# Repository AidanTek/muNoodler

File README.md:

# µNoodler Project
## Technical Files and Info for the µNoodler SAMD21G18A breakout

This project is for me to learn about a number of things, the idea being to build a SAMD21G18A MCU breakout from the ground up that can be used for Circuit Python, MicroPython or Arduino programming. You are welcome to use the files here for anything you want. 

This project was and is possible because of the amazing contributions towards OSH from Adafruit and Arduino - in support, please buy genuine products from these companies!

This is a work in progress! Aidan Taylor 2019

See the installation guide if you have a muNoodler board to experiment with. The Sketch directory provides code examples - contributions are welcome!

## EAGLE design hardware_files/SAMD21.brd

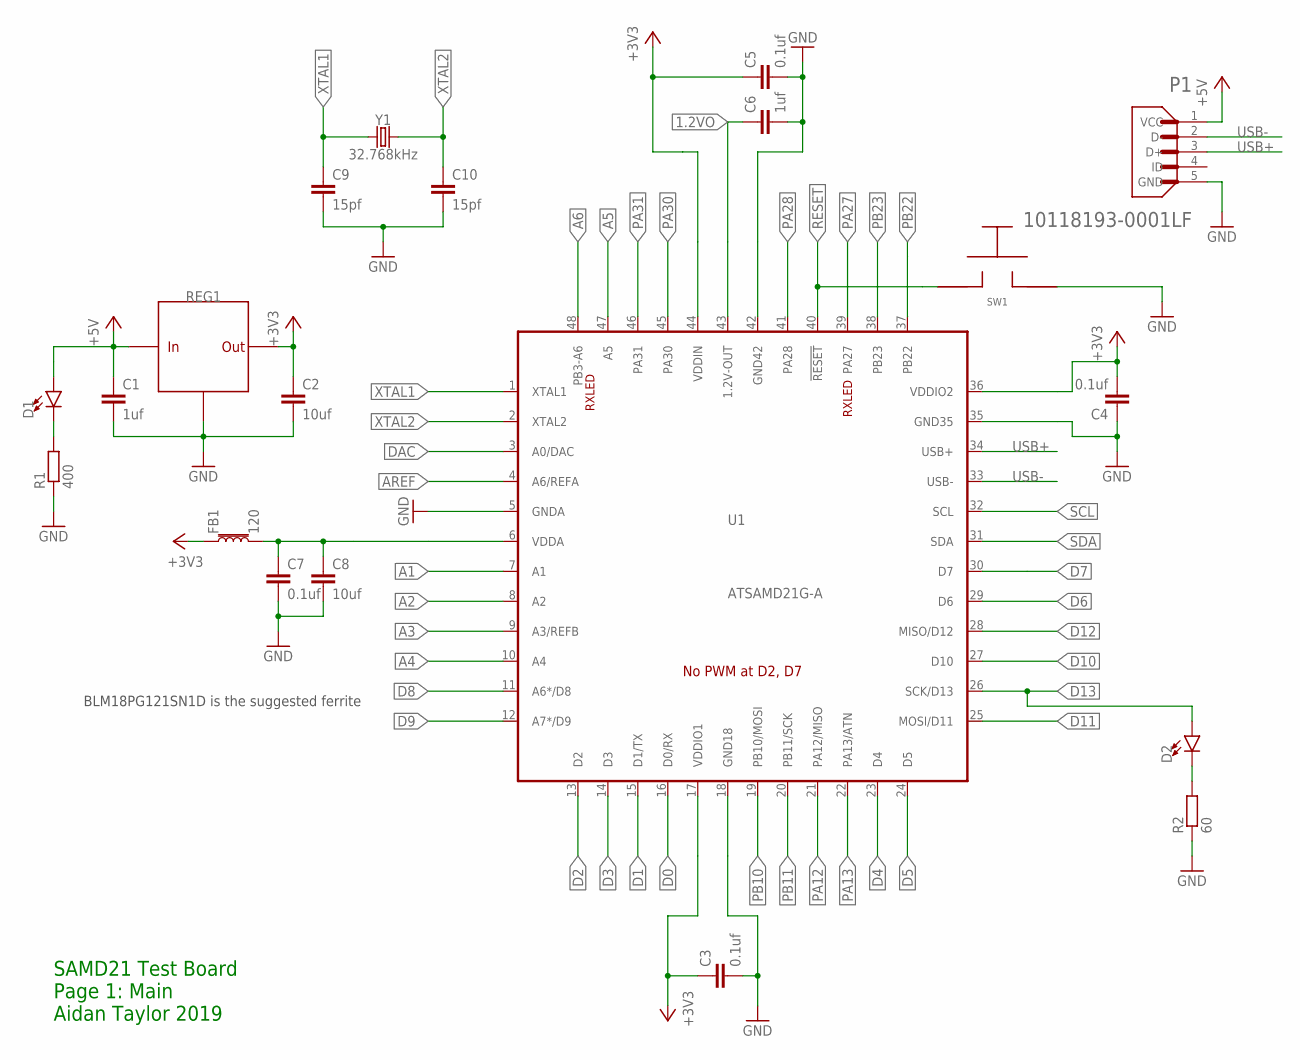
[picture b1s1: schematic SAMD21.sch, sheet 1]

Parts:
C1, C6: 1uf; C0805
C2, C8: 10uf; C0805
C3, C4, C5, C7: 0.1uf; C0603
C9, C10: 15pf; C0603
D1, D2: LED0603; LED-0603
FB1: 120; 0603
P1: 10118193-0001LF; FCI_10118193-0001LF
R1: 400; R0603
R2: 60; R0603
REG1: TLV1117LV33DCYT; SOT223
SW1: KXT3_LOWPROFILE_SMDSWITCH; KXT3_SMD_SWITCH
U1: ATSAMD21G-A; TQFP-48
Y1: 32.768kHz; CRYSTAL-SMD-3.2X1.5MM

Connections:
1.2VO: C6.1, U1.43 (1.2V-OUT); also elsewhere on the board
+3V3: C2.1, C3.1, C4.2, C5.1, FB1.1, REG1.2 (VOUT), REG1.4 (VOUT), U1.17 (VDDIO1), U1.36 (VDDIO2), U1.44 (VDDIN); also elsewhere on the board
+5V: C1.1, D1.A, P1.1 (VCC), REG1.3 (VIN); also elsewhere on the board
A1: U1.7 (A1); also elsewhere on the board
A2: U1.8 (A2); also elsewhere on the board
A3: U1.9 (A3/REFB); also elsewhere on the board
A4: U1.10 (A4); also elsewhere on the board
A5: U1.47 (A5); also elsewhere on the board
A6: U1.48 (PB3-A6); also elsewhere on the board
AREF: U1.4 (A6/REFA); also elsewhere on the board
D0: U1.16 (D0/RX); also elsewhere on the board
D1: U1.15 (D1/TX); also elsewhere on the board
D2: U1.13 (D2); also elsewhere on the board
D3: U1.14 (D3); also elsewhere on the board
D4: U1.23 (D4); also elsewhere on the board
D5: U1.24 (D5); also elsewhere on the board
D6: U1.29 (D6); also elsewhere on the board
D7: U1.30 (D7); also elsewhere on the board
D8: U1.11 (A6*/D8); also elsewhere on the board
D9: U1.12 (A7*/D9); also elsewhere on the board
D10: U1.27 (D10); also elsewhere on the board
D11: U1.25 (MOSI/D11); also elsewhere on the board
D12: U1.28 (MISO/D12); also elsewhere on the board
D13: D2.A, U1.26 (SCK/D13); also elsewhere on the board
DAC: U1.3 (A0/DAC); also elsewhere on the board
GND: C1.2, C2.2, C3.2, C4.1, C5.2, C6.2, C7.2, C8.2, C9.2, C10.2, P1.5 (GND), R1.1, R2.1, REG1.1 (GND), SW1.P$2, U1.5 (GNDA), U1.18 (GND18), U1.35 (GND35), U1.42 (GND42); also elsewhere on the board
unnamed: C7.1, C8.1, FB1.2, U1.6 (VDDA)
unnamed: D1.C, R1.2
unnamed: D2.C, R2.2
PA12: U1.21 (PA12/MISO); also elsewhere on the board
PA13: U1.22 (PA13/ATN); also elsewhere on the board
PA27: U1.39 (PA27)
PA28: U1.41 (PA28)
PA30: U1.45 (PA30); also elsewhere on the board
PA31: U1.46 (PA31); also elsewhere on the board
PB10: U1.19 (PB10/MOSI); also elsewhere on the board
PB11: U1.20 (PB11/SCK); also elsewhere on the board
PB22: U1.37 (PB22); also elsewhere on the board
PB23: U1.38 (PB23); also elsewhere on the board
RESET: SW1.P$1, U1.40 (!RESET!); also elsewhere on the board
SCL: U1.32 (SCL); also elsewhere on the board
SDA: U1.31 (SDA); also elsewhere on the board
USB+: P1.3 (D+), U1.34 (USB+)
USB-: P1.2 (D-), U1.33 (USB-)
XTAL1: C9.1, U1.1 (XTAL1), Y1.P$1 (1)
XTAL2: C10.1, U1.2 (XTAL2), Y1.P$2 (2)

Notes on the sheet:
BLM18PG121SN1D is the suggested ferrite
SAMD21 Test Board Page 1: Main Aidan Taylor 2019

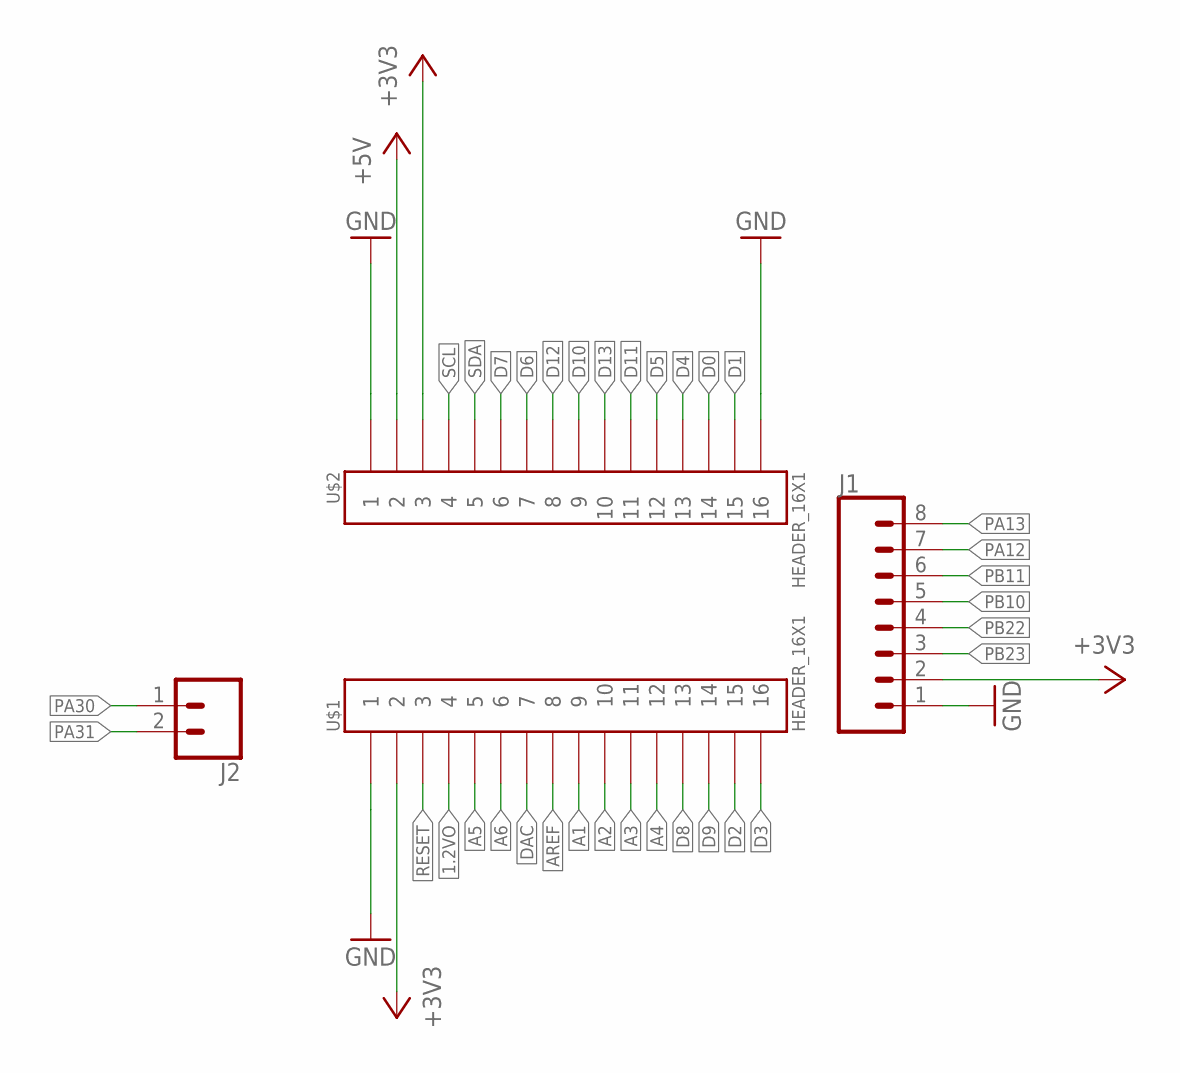
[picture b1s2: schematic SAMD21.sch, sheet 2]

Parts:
J1: CONN_08"; 1X08
J2: CONN_02; 1X02
U$1, U$2: HEADER_16X1; HDRV16W64P254_1X16_4064X254X900B_NO_SILK

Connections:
1.2VO: U$1.P$4 (4); also elsewhere on the board
+3V3: J1.2, U$1.P$2 (2), U$2.P$3 (3); also elsewhere on the board
+5V: U$2.P$2 (2); also elsewhere on the board
A1: U$1.P$9 (9); also elsewhere on the board
A2: U$1.P$10 (10); also elsewhere on the board
A3: U$1.P$11 (11); also elsewhere on the board
A4: U$1.P$12 (12); also elsewhere on the board
A5: U$1.P$5 (5); also elsewhere on the board
A6: U$1.P$6 (6); also elsewhere on the board
AREF: U$1.P$8 (8); also elsewhere on the board
D0: U$2.P$14 (14); also elsewhere on the board
D1: U$2.P$15 (15); also elsewhere on the board
D2: U$1.P$15 (15); also elsewhere on the board
D3: U$1.P$16 (16); also elsewhere on the board
D4: U$2.P$13 (13); also elsewhere on the board
D5: U$2.P$12 (12); also elsewhere on the board
D6: U$2.P$7 (7); also elsewhere on the board
D7: U$2.P$6 (6); also elsewhere on the board
D8: U$1.P$13 (13); also elsewhere on the board
D9: U$1.P$14 (14); also elsewhere on the board
D10: U$2.P$9 (9); also elsewhere on the board
D11: U$2.P$11 (11); also elsewhere on the board
D12: U$2.P$8 (8); also elsewhere on the board
D13: U$2.P$10 (10); also elsewhere on the board
DAC: U$1.P$7 (7); also elsewhere on the board
GND: J1.1, U$1.P$1 (1), U$2.P$1 (1), U$2.P$16 (16); also elsewhere on the board
PA12: J1.7; also elsewhere on the board
PA13: J1.8; also elsewhere on the board
PA30: J2.1; also elsewhere on the board
PA31: J2.2; also elsewhere on the board
PB10: J1.5; also elsewhere on the board
PB11: J1.6; also elsewhere on the board
PB22: J1.4; also elsewhere on the board
PB23: J1.3; also elsewhere on the board
RESET: U$1.P$3 (3); also elsewhere on the board
SCL: U$2.P$4 (4); also elsewhere on the board
SDA: U$2.P$5 (5); also elsewhere on the board

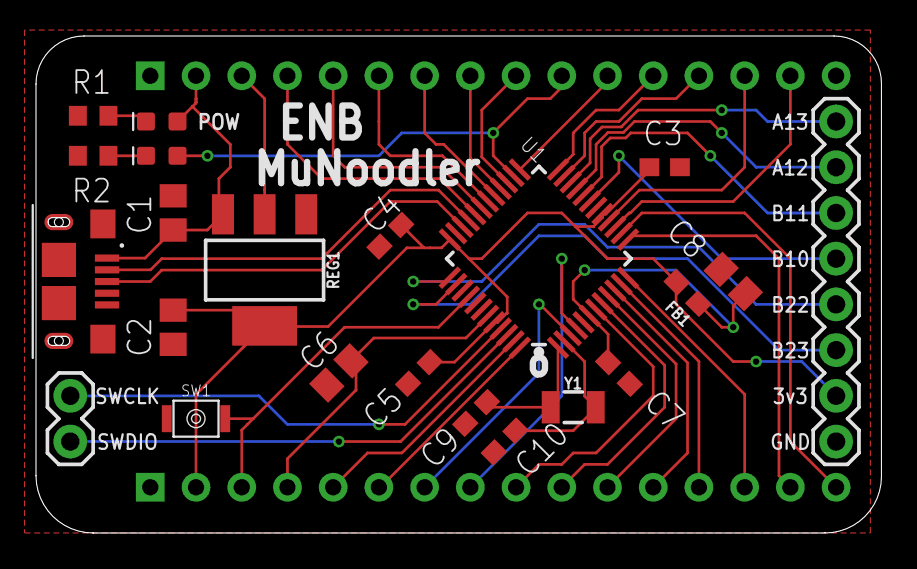
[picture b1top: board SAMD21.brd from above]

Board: 2 copper layers, 47.0 x 27.6 mm, 24 parts (0 on the bottom side), 44 nets.

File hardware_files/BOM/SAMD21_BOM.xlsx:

Qty | Value | Device | Package | Parts | Description | AVAILABILITY | DESCRIPTION | MF | MP | PACKAGE | PRICE | PROD_ID | SPICEPREFIX | VALUE
1 |  | CONN_08";1X08" | J1 | Multi connection point. Often used as Generic Header-pin footprint for 0.1 inch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 |  |  |  |  |  |  | CONN-08438
2 |  | LED0603 | LED-0603 | D1, D2 | LED (Generic)
2 |  | R-EU_R0603 | R0603 | R1, R2 | RESISTOR, European symbol |  |  |  |  |  |  |  | R
4 | 0.1uf | C-EUC0603 | C0603 | C3, C4, C5, C7 | CAPACITOR, European symbol |  |  |  |  |  |  |  | C
1 | 10118193-0001LF | 10118193-0001LF | FCI_10118193-0001LF | P1 | Micro USB B Type Receptacle | Unavailable | Conn Micro USB Type B RCP 5 POS 0.65mm Solder RA SMD 5 Terminal 1 Port T/R | Amphenol FCI | 10118193-0001LF | None | None
2 | 10uf | C-EUC0805 | C0805 | C2, C8 | CAPACITOR, European symbol |  |  |  |  |  |  |  | C
1 | 120 | FERRITE_BEAD-0603 | 603 | FB1 | Ferrite Bead (blocks, cores, rings, chokes, etc.) |  |  |  |  |  |  | NDUC-13805 |  | 30Œ©/1.8A
2 | 15pf | C-EUC0603 | C0603 | C9, C10 | CAPACITOR, European symbol |  |  |  |  |  |  |  | C
2 | 1uf | C-EUC0805 | C0805 | C1, C6 | CAPACITOR, European symbol |  |  |  |  |  |  |  | C
1 | 32.768kHz | CRYSTAL-32.768KHZSMD-3.2X1.5 | CRYSTAL-SMD-3.2X1.5MM | Y1 | 32.768kHz Crystal |  |  |  |  |  |  | XTAL-13062 |  | 32.768kHz
1 | ATSAMD21G-A | ATSAMD21G-A | TQFP-48 | U1 | Atmel SAMD21G SMART ARM-Based Microcontroller |  |  |  |  |  |  | IC-13064
2 | HEADER_16X1 | HEADER_16X1 | HDRV16W64P254_1X16_4064X254X900B_NO_SILK | U$1, U$2
1 | KXT3_LOWPROFILE_SMDSWITCH | KXT3_LOWPROFILE_SMDSWITCH | KXT3_SMD_SWITCH | SW1
1 | TLV1117LV33DCYT | TLV1117LV33DCYT | SOT223 | REG1

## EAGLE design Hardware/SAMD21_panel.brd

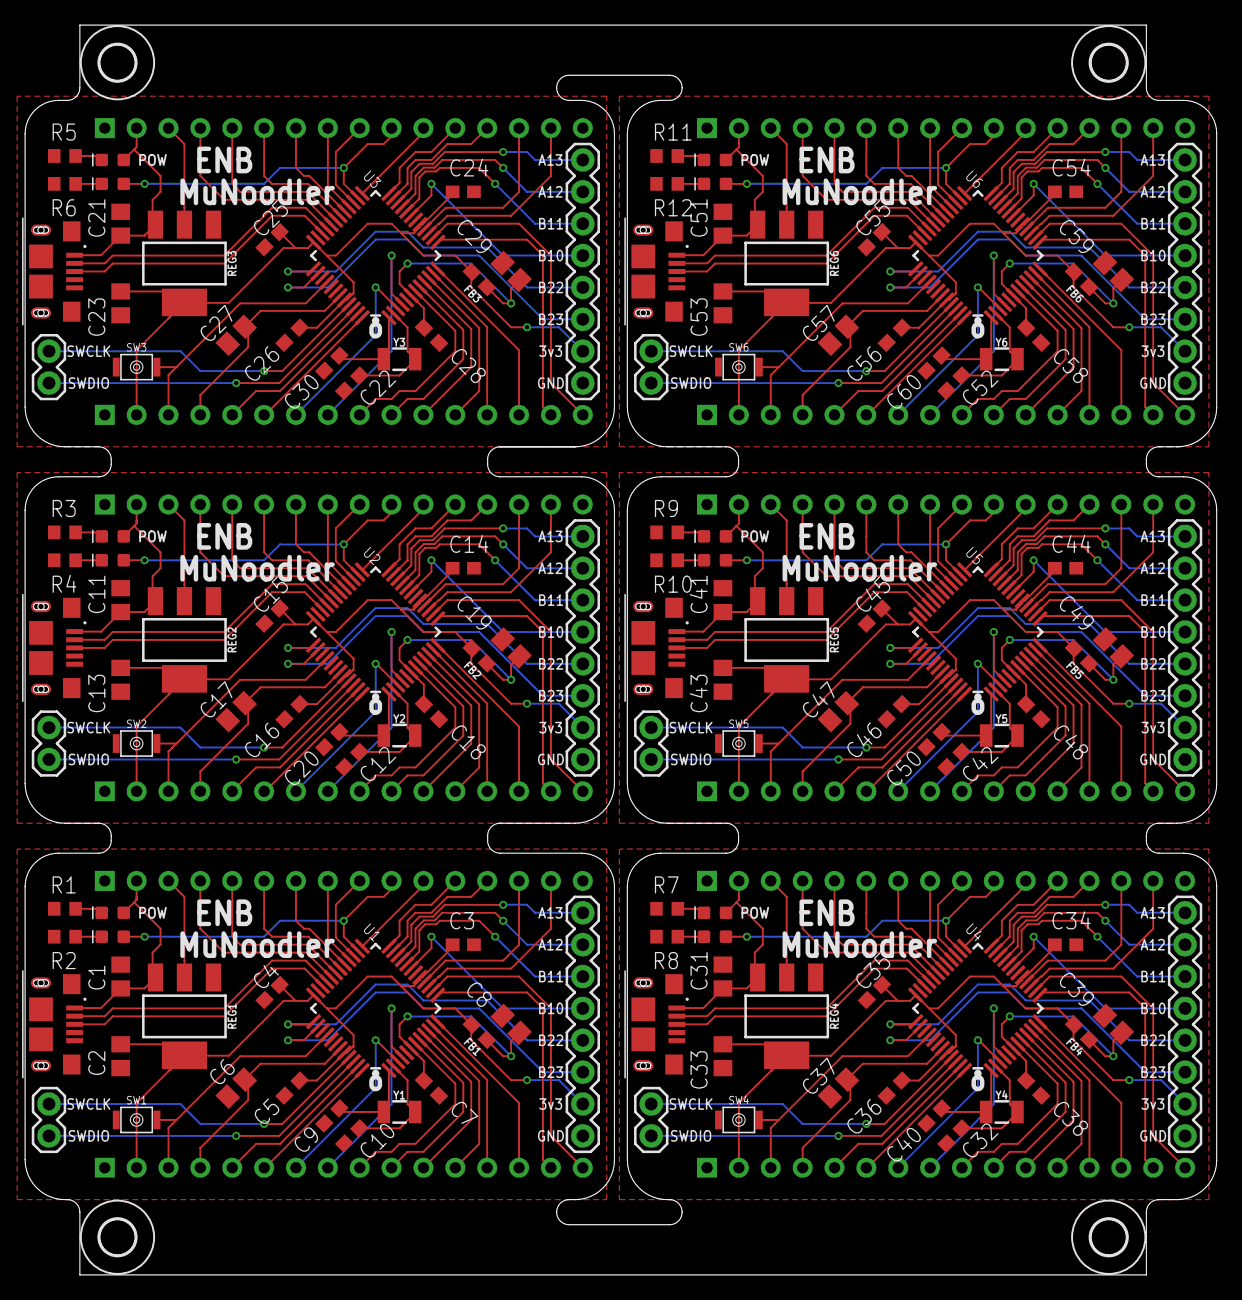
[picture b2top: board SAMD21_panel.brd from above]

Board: 2 copper layers, 95.0 x 99.6 mm, 148 parts (0 on the bottom side), 264 nets.

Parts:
C1, C6, C11, C17, C21, C27, C31, C37, C41, C47, C51, C57: 1uf; C0805
C2, C8, C13, C19, C23, C29, C33, C39, C43, C49, C53, C59: 10uf; C0805
C3, C4, C5, C7, C14, C15, C16, C18, C24, C25, C26, C28, C34, C35, C36, C38, C44, C45, C46, C48, C54, C55, C56, C58: 0.1uf; C0603
C9, C10, C12, C20, C22, C30, C32, C40, C42, C50, C52, C60: 15pf; C0603
D1, D2, D3, D4, D5, D6, D7, D8, D9, D10, D11, D12: LED-0603
E$1, E$2, E$3, E$4: 2,8
FB1, FB2, FB3, FB4, FB5, FB6: 120; 0603
J1, J3, J5, J7, J9, J11: 1X08
J2, J4, J6, J8, J10, J12: 1X02
P1, P2, P3, P4, P5, P6: 10118193-0001LF; FCI_10118193-0001LF
R1, R3, R5, R7, R9, R11: 400; R0603
R2, R4, R6, R8, R10, R12: 60; R0603
REG1, REG2, REG3, REG4, REG5, REG6: TLV1117LV33DCYT; SOT223
SW1, SW2, SW3, SW4, SW5, SW6: KXT3_LOWPROFILE_SMDSWITCH; KXT3_SMD_SWITCH
U1, U2, U3, U4, U5, U6: ATSAMD21G-A; TQFP-48
U$1, U$2, U$3, U$4, U$5, U$6, U$7, U$8, U$9, U$10, U$11, U$12: HEADER_16X1; HDRV16W64P254_1X16_4064X254X900B_NO_SILK
Y1, Y2, Y3, Y4, Y5, Y6: 32.768kHz; CRYSTAL-SMD-3.2X1.5MM

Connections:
1.2VO: C6.1, U1.43, U$1.P$4
1.2VO1: C17.1, U2.43, U$3.P$4
1.2VO2: C27.1, U3.43, U$5.P$4
1.2VO3: C37.1, U4.43, U$7.P$4
1.2VO4: C47.1, U5.43, U$9.P$4
1.2VO5: C57.1, U6.43, U$11.P$4
+3V1: C13.1, C14.1, C15.2, C16.1, FB2.1, J3.2, REG2.2, REG2.4, U2.17, U2.36, U2.44, U$3.P$2, U$4.P$3
+3V2: C23.1, C24.1, C25.2, C26.1, FB3.1, J5.2, REG3.2, REG3.4, U3.17, U3.36, U3.44, U$5.P$2, U$6.P$3
+3V3: C2.1, C3.1, C4.2, C5.1, FB1.1, J1.2, REG1.2, REG1.4, U1.17, U1.36, U1.44, U$1.P$2, U$2.P$3
+3V4: C33.1, C34.1, C35.2, C36.1, FB4.1, J7.2, REG4.2, REG4.4, U4.17, U4.36, U4.44, U$7.P$2, U$8.P$3
+3V5: C43.1, C44.1, C45.2, C46.1, FB5.1, J9.2, REG5.2, REG5.4, U5.17, U5.36, U5.44, U$9.P$2, U$10.P$3
+3V6: C53.1, C54.1, C55.2, C56.1, FB6.1, J11.2, REG6.2, REG6.4, U6.17, U6.36, U6.44, U$11.P$2, U$12.P$3
+5V: C1.1, D1.A, P1.1, REG1.3, U$2.P$2
+5V1: C11.1, D3.A, P2.1, REG2.3, U$4.P$2
+5V2: C21.1, D5.A, P3.1, REG3.3, U$6.P$2
+5V3: C31.1, D7.A, P4.1, REG4.3, U$8.P$2
+5V4: C41.1, D9.A, P5.1, REG5.3, U$10.P$2
+5V5: C51.1, D11.A, P6.1, REG6.3, U$12.P$2
A1: U1.7, U$1.P$9
A2: U1.8, U$1.P$10
A3: U1.9, U$1.P$11
A4: U1.10, U$1.P$12
A5: U1.47, U$1.P$5
A6: U1.48, U$1.P$6
A7: U2.48, U$3.P$6
A8: U2.7, U$3.P$9
A9: U2.8, U$3.P$10
A10: U2.9, U$3.P$11
A11: U2.10, U$3.P$12
A12: U2.47, U$3.P$5
A13: U3.48, U$5.P$6
A14: U3.7, U$5.P$9
A15: U3.8, U$5.P$10
A16: U3.9, U$5.P$11
A17: U3.10, U$5.P$12
A18: U3.47, U$5.P$5
A19: U4.48, U$7.P$6
A20: U4.7, U$7.P$9
A21: U4.8, U$7.P$10
A22: U4.9, U$7.P$11
A23: U4.10, U$7.P$12
A24: U4.47, U$7.P$5
A25: U5.48, U$9.P$6
A26: U5.7, U$9.P$9
A27: U5.8, U$9.P$10
A28: U5.9, U$9.P$11
A29: U5.10, U$9.P$12
A30: U5.47, U$9.P$5
A31: U6.48, U$11.P$6
A32: U6.7, U$11.P$9
A33: U6.8, U$11.P$10
A34: U6.9, U$11.P$11
A35: U6.10, U$11.P$12
A36: U6.47, U$11.P$5
AREF: U1.4, U$1.P$8
AREF1: U2.4, U$3.P$8
AREF2: U3.4, U$5.P$8
AREF3: U4.4, U$7.P$8
AREF4: U5.4, U$9.P$8
AREF5: U6.4, U$11.P$8
D0: U1.16, U$2.P$14
D1: U1.15, U$2.P$15
D2: U1.13, U$1.P$15
D3: U1.14, U$1.P$16
D4: U1.23, U$2.P$13
D5: U1.24, U$2.P$12
D6: U1.29, U$2.P$7
D7: U1.30, U$2.P$6
D8: U1.11, U$1.P$13
D9: U1.12, U$1.P$14
D10: U1.27, U$2.P$9
D11: U1.25, U$2.P$11
D12: U1.28, U$2.P$8
D13: D2.A, U1.26, U$2.P$10
D14: U2.12, U$3.P$14
D15: U2.13, U$3.P$15
D16: U2.14, U$3.P$16
D17: U2.15, U$4.P$15
D18: U2.16, U$4.P$14
D19: U2.23, U$4.P$13
D20: U2.24, U$4.P$12
D21: U2.25, U$4.P$11
D22: D4.A, U2.26, U$4.P$10
D23: U2.27, U$4.P$9
D24: U2.28, U$4.P$8
D25: U2.29, U$4.P$7
D26: U2.30, U$4.P$6
D27: U2.11, U$3.P$13
D28: U3.12, U$5.P$14
D29: U3.13, U$5.P$15
D30: U3.14, U$5.P$16
D31: U3.15, U$6.P$15
D32: U3.16, U$6.P$14
D33: U3.23, U$6.P$13
D34: U3.24, U$6.P$12
D35: U3.25, U$6.P$11
D36: D6.A, U3.26, U$6.P$10
D37: U3.27, U$6.P$9
D38: U3.28, U$6.P$8
D39: U3.29, U$6.P$7
D40: U3.30, U$6.P$6
D41: U3.11, U$5.P$13
D42: U4.12, U$7.P$14
D43: U4.13, U$7.P$15
D44: U4.14, U$7.P$16
D45: U4.15, U$8.P$15
D46: U4.16, U$8.P$14
D47: U4.23, U$8.P$13
D48: U4.24, U$8.P$12
D49: U4.25, U$8.P$11
D50: D8.A, U4.26, U$8.P$10
D51: U4.27, U$8.P$9
D52: U4.28, U$8.P$8
D53: U4.29, U$8.P$7
D54: U4.30, U$8.P$6
D55: U4.11, U$7.P$13
D56: U5.12, U$9.P$14
D57: U5.13, U$9.P$15
D58: U5.14, U$9.P$16
D59: U5.15, U$10.P$15
D60: U5.16, U$10.P$14
D61: U5.23, U$10.P$13
D62: U5.24, U$10.P$12
D63: U5.25, U$10.P$11
D64: D10.A, U5.26, U$10.P$10
D65: U5.27, U$10.P$9
D66: U5.28, U$10.P$8
D67: U5.29, U$10.P$7
D68: U5.30, U$10.P$6
D69: U5.11, U$9.P$13
D70: U6.12, U$11.P$14
D71: U6.13, U$11.P$15
D72: U6.14, U$11.P$16
D73: U6.15, U$12.P$15
D74: U6.16, U$12.P$14
D75: U6.23, U$12.P$13
D76: U6.24, U$12.P$12
D77: U6.25, U$12.P$11
D78: D12.A, U6.26, U$12.P$10
D79: U6.27, U$12.P$9
D80: U6.28, U$12.P$8
D81: U6.29, U$12.P$7
D82: U6.30, U$12.P$6
D83: U6.11, U$11.P$13
DAC: U1.3, U$1.P$7
DAC1: U2.3, U$3.P$7
DAC2: U3.3, U$5.P$7
DAC3: U4.3, U$7.P$7
DAC4: U5.3, U$9.P$7
DAC5: U6.3, U$11.P$7
GND: C1.2, C2.2, C3.2, C4.1, C5.2, C6.2, C7.2, C8.2, C9.2, C10.2, J1.1, P1.5, R1.1, R2.1, REG1.1, SW1.P$2, U1.5, U1.18, U1.35, U1.42, U$1.P$1, U$2.P$1, U$2.P$16
GND1: C11.2, C12.2, C13.2, C14.2, C15.1, C16.2, C17.2, C18.2, C19.2, C20.2, J3.1, P2.5, R3.1, R4.1, REG2.1, SW2.P$2, U2.5, U2.18, U2.35, U2.42, U$3.P$1, U$4.P$1, U$4.P$16
GND2: C21.2, C22.2, C23.2, C24.2, C25.1, C26.2, C27.2, C28.2, C29.2, C30.2, J5.1, P3.5, R5.1, R6.1, REG3.1, SW3.P$2, U3.5, U3.18, U3.35, U3.42, U$5.P$1, U$6.P$1, U$6.P$16
GND3: C31.2, C32.2, C33.2, C34.2, C35.1, C36.2, C37.2, C38.2, C39.2, C40.2, J7.1, P4.5, R7.1, R8.1, REG4.1, SW4.P$2, U4.5, U4.18, U4.35, U4.42, U$7.P$1, U$8.P$1, U$8.P$16
GND4: C41.2, C42.2, C43.2, C44.2, C45.1, C46.2, C47.2, C48.2, C49.2, C50.2, J9.1, P5.5, R9.1, R10.1, REG5.1, SW5.P$2, U5.5, U5.18, U5.35, U5.42, U$9.P$1, U$10.P$1, U$10.P$16
GND5: C51.2, C52.2, C53.2, C54.2, C55.1, C56.2, C57.2, C58.2, C59.2, C60.2, J11.1, P6.5, R11.1, R12.1, REG6.1, SW6.P$2, U6.5, U6.18, U6.35, U6.42, U$11.P$1, U$12.P$1, U$12.P$16
unnamed: C7.1, C8.1, FB1.2, U1.6
unnamed: D1.C, R1.2
unnamed: D2.C, R2.2
unnamed: C18.1, C19.1, FB2.2, U2.6
unnamed: D3.C, R3.2
unnamed: D4.C, R4.2
unnamed: C28.1, C29.1, FB3.2, U3.6
unnamed: D5.C, R5.2
unnamed: D6.C, R6.2
unnamed: C38.1, C39.1, FB4.2, U4.6
unnamed: D7.C, R7.2
unnamed: D8.C, R8.2
unnamed: C48.1, C49.1, FB5.2, U5.6
unnamed: D9.C, R9.2
unnamed: D10.C, R10.2
unnamed: C58.1, C59.1, FB6.2, U6.6
unnamed: D11.C, R11.2
unnamed: D12.C, R12.2
PA1: J3.7, U2.21
PA2: J3.8, U2.22
PA5: J4.1, U2.45
PA6: J4.2, U2.46
PA7: J5.7, U3.21
PA8: J5.8, U3.22
PA11: J6.1, U3.45
PA12: J1.7, U1.21
PA13: J1.8, U1.22
PA14: J6.2, U3.46
PA15: J7.7, U4.21
PA16: J7.8, U4.22
PA19: J8.1, U4.45
PA20: J8.2, U4.46
PA21: J9.7, U5.21
PA22: J9.8, U5.22
PA25: J10.1, U5.45
PA26: J10.2, U5.46
PA29: J11.7, U6.21
PA30: J2.1, U1.45
PA31: J2.2, U1.46
PA32: J11.8, U6.22
PA35: J12.1, U6.45
PA36: J12.2, U6.46
PB1: J3.5, U2.19
PB2: J3.6, U2.20
PB3: J3.4, U2.37
PB4: J3.3, U2.38
PB5: J5.5, U3.19
PB6: J5.6, U3.20
PB7: J5.4, U3.37
PB8: J5.3, U3.38
PB9: J7.5, U4.19
PB10: J1.5, U1.19
PB11: J1.6, U1.20
PB12: J7.6, U4.20
PB13: J7.4, U4.37
PB14: J7.3, U4.38
PB15: J9.5, U5.19
PB16: J9.6, U5.20
PB17: J9.4, U5.37
PB18: J9.3, U5.38
PB19: J11.5, U6.19
PB20: J11.6, U6.20
PB21: J11.4, U6.37
PB22: J1.4, U1.37
PB23: J1.3, U1.38
PB24: J11.3, U6.38
RESET: SW1.P$1, U1.40, U$1.P$3
RESET1: SW2.P$1, U2.40, U$3.P$3
RESET2: SW3.P$1, U3.40, U$5.P$3
RESET3: SW4.P$1, U4.40, U$7.P$3
RESET4: SW5.P$1, U5.40, U$9.P$3
RESET5: SW6.P$1, U6.40, U$11.P$3
SCL: U1.32, U$2.P$4
SCL1: U2.32, U$4.P$4
SCL2: U3.32, U$6.P$4
SCL3: U4.32, U$8.P$4
SCL4: U5.32, U$10.P$4
SCL5: U6.32, U$12.P$4
SDA: U1.31, U$2.P$5
SDA1: U2.31, U$4.P$5
SDA2: U3.31, U$6.P$5
SDA3: U4.31, U$8.P$5
SDA4: U5.31, U$10.P$5
SDA5: U6.31, U$12.P$5
USB+: P1.3, U1.34
USB+1: P2.3, U2.34
USB+2: P3.3, U3.34
USB+3: P4.3, U4.34
USB+4: P5.3, U5.34
USB+5: P6.3, U6.34
USB-: P1.2, U1.33
USB-1: P2.2, U2.33
USB-2: P3.2, U3.33
USB-3: P4.2, U4.33
USB-4: P5.2, U5.33
USB-5: P6.2, U6.33
XTAL1: C9.1, U1.1, Y1.P$1
XTAL2: C10.1, U1.2, Y1.P$2
XTAL3: C20.1, U2.1, Y2.P$1
XTAL4: C12.1, U2.2, Y2.P$2
XTAL5: C30.1, U3.1, Y3.P$1
XTAL6: C22.1, U3.2, Y3.P$2
XTAL7: C40.1, U4.1, Y4.P$1
XTAL8: C32.1, U4.2, Y4.P$2
XTAL9: C50.1, U5.1, Y5.P$1
XTAL10: C42.1, U5.2, Y5.P$2
XTAL11: C60.1, U6.1, Y6.P$1
XTAL12: C52.1, U6.2, Y6.P$2

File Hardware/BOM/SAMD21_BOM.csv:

"Qty";"Value";"Device";"Package";"Parts";"Description";"AVAILABILITY";"DESCRIPTION";"MF";"MP";"PACKAGE";"PRICE";"PROD_ID";"SPICEPREFIX";"VALUE";
"1";"";"CONN_08"";"1X08";"J1";"Multi connection point. Often used as Generic Header-pin footprint for 0.1 inch spaced/style header connections";"";"";"";"";"";"";"CONN-08438";"";"";
"2";"";"LED0603";"LED-0603";"D1, D2";"LED (Generic)";"";"";"";"";"";"";"";"";"";
"2";"";"R-EU_R0603";"R0603";"R1, R2";"RESISTOR, European symbol";"";"";"";"";"";"";"";"R";"";
"4";"0.1uf";"C-EUC0603";"C0603";"C3, C4, C5, C7";"CAPACITOR, European symbol";"";"";"";"";"";"";"";"C";"";
"1";"10118193-0001LF";"10118193-0001LF";"FCI_10118193-0001LF";"P1";"Micro USB B Type Receptacle";"Unavailable";" Conn Micro USB Type B RCP 5 POS 0.65mm Solder RA SMD 5 Terminal 1 Port T/R ";"Amphenol FCI";"10118193-0001LF";"None";"None";"";"";"";
"2";"10uf";"C-EUC0805";"C0805";"C2, C8";"CAPACITOR, European symbol";"";"";"";"";"";"";"";"C";"";
"1";"120";"FERRITE_BEAD-0603";"0603";"FB1";"Ferrite Bead (blocks, cores, rings, chokes, etc.)";"";"";"";"";"";"";"NDUC-13805";"";"30Ω/1.8A";
"2";"15pf";"C-EUC0603";"C0603";"C9, C10";"CAPACITOR, European symbol";"";"";"";"";"";"";"";"C";"";
"2";"1uf";"C-EUC0805";"C0805";"C1, C6";"CAPACITOR, European symbol";"";"";"";"";"";"";"";"C";"";
"1";"32.768kHz";"CRYSTAL-32.768KHZSMD-3.2X1.5";"CRYSTAL-SMD-3.2X1.5MM";"Y1";"32.768kHz Crystal";"";"";"";"";"";"";"XTAL-13062";"";"32.768kHz";
"1";"ATSAMD21G-A";"ATSAMD21G-A";"TQFP-48";"U1";"Atmel SAMD21G SMART ARM-Based Microcontroller";"";"";"";"";"";"";"IC-13064";"";"";
"2";"HEADER_16X1";"HEADER_16X1";"HDRV16W64P254_1X16_4064X254X900B_NO_SILK";"U$1, U$2";"";"";"";"";"";"";"";"";"";"";
"1";"KXT3_LOWPROFILE_SMDSWITCH";"KXT3_LOWPROFILE_SMDSWITCH";"KXT3_SMD_SWITCH";"SW1";"";"";"";"";"";"";"";"";"";"";
"1";"TLV1117LV33DCYT";"TLV1117LV33DCYT";"SOT223";"REG1";"";"";"";"";"";"";"";"";"";"";

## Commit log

2019-03-15 init commit
2019-03-15 README.md fix
2019-03-15 Create LICENSE
2019-03-15 LICENSE.md and README.md updates
2019-03-15 Eagle project files added
2019-03-26 Arduino board configuration added
2019-03-26 fixing code quotations
2019-03-26 updates for online installation to board installer .json
2019-03-26 fix attempt online boards installation
2019-03-26 Change to link for munoodler.zip
    For some reason, Arduino is not happy using the .zip file, link to raw may fix
2019-03-26 installation guide added
2019-03-29 OpenOCD Bootloader added
2019-03-31 Sketch directory added
2019-03-31 max msp examples added
2019-04-01 MaxMSP Serial Output examples added
2019-04-01 MaxMSP addressable LED control examples Added
2019-04-16 Addressable LED MaxMSP Interface added

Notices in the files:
parts and their libraries:
SparkFun-Coils: Licensing: Creative Commons ShareAlike 4.0 International - https://creativecommons.org/licenses/by-sa/4.0
